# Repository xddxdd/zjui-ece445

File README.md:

Air Quality Sensing Network
===========================

Cloud Server Installation
-------------------------

1. I do not recommend using a cloud server located in mainland China, since then you need to register with the government (备案) to host a website.
   - You may choose servers located in Hong Kong, for example.
2. Install InfluxDB
   - [https://docs.influxdata.com/influxdb/v1.8/introduction/install/](https://docs.influxdata.com/influxdb/v1.8/introduction/install/)
3. Create a database named `air_quality`.
4. Create 3 users:
   - [https://docs.influxdata.com/influxdb/v1.8/administration/authentication_and_authorization/](https://docs.influxdata.com/influxdb/v1.8/administration/authentication_and_authorization/)
   - The first is administrator for InfluxDB server.
   - The second is for sensors to upload data.
     - Username: `***REMOVED***`
     - Password: `***REMOVED***`
   - The third is for website system to read data.
     - Username: `***REMOVED***`
     - Password: `***REMOVED***`
5. Make sure you can access InfluxDB via `[Server IP]:8086`.

STM32 Installation
------------------

1. Modify `stm32/Src/run.h`:
   - Change `HTTP_INFLUXDB_IP` etc to point to your cloud server
   - If you changed username or password for the upload user, also update them here
   - Change `ZJUWLAN_USERNAME` and `ZJUWLAN_PASSWORD` to your own, for auto login to ZJU Wi-Fi
2. Run `make` in `stm32` directory.
   - I'm assuming you use Mac or Linux. I never tried to compile the project on Windows.
   - You need to download GNU Arm Embedded Toolchain.
3. Put the jumper on the top of STM32 (closer to the 4 unsoldered holes) to right, to enter download mode
4. Connect a serial to USB converter:
   - PA9 (GPS module's TX) - Converter's RX
   - PA10 (GPS module's RX) - Converter's TX
   - Ground pin (choose any one) - Converter's GND
5. Run following command to flash program to STM32:
   - `stm32flash /dev/ttyUSB0 -w build/stm32.bin -v -g 0x0`
   - Now the program should start running
6. If you want to put STM32 to field-test, put the jumper on the top of STM32 to left, to enter normal working mode
   - Now STM32 will start running the flashed program once power is on
7. You can use STM32CubeMX to open the `stm32/stm32.ioc` project to change pin definition, regenerate library code, etc.

Web Server Installation
-----------------------

1. Install nginx and PHP on the cloud server:
   - [https://www.digitalocean.com/community/tutorials/how-to-install-linux-nginx-mysql-php-lemp-stack-ubuntu-18-04](https://www.digitalocean.com/community/tutorials/how-to-install-linux-nginx-mysql-php-lemp-stack-ubuntu-18-04)
   - Point website root folder to `webpage` folder.
2. Install Python 3 on the server, and libraries that are needed:
   - `apt install python3 python3-pip python3-numpy python3-matplotlib `
   - `pip3 install influxdb windrose`
3. Enter `python` directory, run `python3 run.py` to refresh website.
   - Remember to update InfluxDB address/user/password in `fetch.py`.
   - Use tools such as Cron or Systemd to run it periodically.
4. Run `python3 weatherlink.py` to crawl wind direction & speed from weather station and upload to InfluxDB.
   - Also remember to update InfluxDB address/user/password in `weatherlink.py`.
   - Use tools such as Supervisord or Systemd to run it continuously.

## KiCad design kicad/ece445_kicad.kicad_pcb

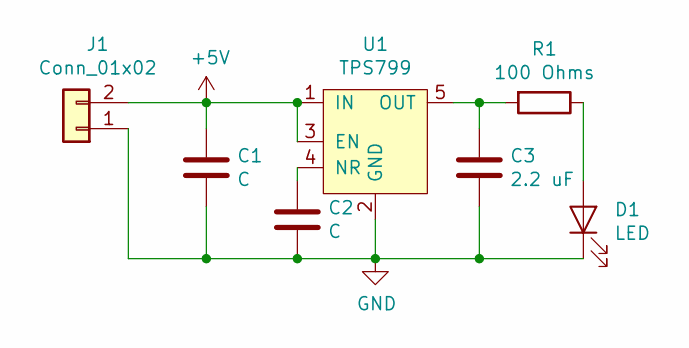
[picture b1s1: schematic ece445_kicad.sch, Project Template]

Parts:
C1, C2: C; CP_Radial_D5.0mm_P2.50mm
C3: 2.2 uF; CP_Radial_D5.0mm_P2.50mm
D1: LED; LED_Rectangular_W5.0mm_H2.0mm
J1: Conn_01x02; PinHeader_1x02_P2.54mm_Vertical
R1: 100 Ohms; R_Axial_DIN0204_L3.6mm_D1.6mm_P5.08mm_Horizontal
U1: TPS799

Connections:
+5V: C1.1, J1.2, U1.1 (IN), U1.3 (EN)
GND: C1.2, C2.2, C3.2, D1.1 (K), J1.1, U1.2 (GND)
unnamed: C2.1, U1.4 (NR)
unnamed: C3.1, R1.2, U1.5 (OUT)
unnamed: D1.2 (A), R1.1

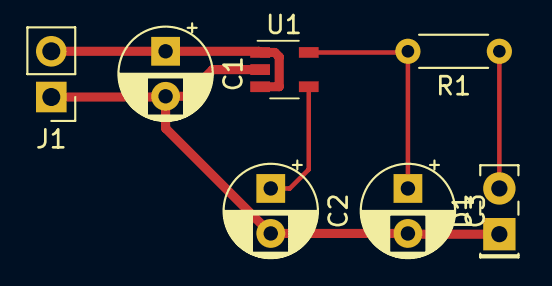
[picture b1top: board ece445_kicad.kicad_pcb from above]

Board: 2 copper layers, 7 parts (0 on the bottom side), 5 nets.

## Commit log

2020-03-21 PCB assignment
2020-03-31 stm32: blinker working
2020-03-31 stm32: i2c work in progress
2020-03-31 stm32: bme680 almost working
2020-03-31 stm32: bme680 fully working
2020-03-31 stm32: remove build files from repo
2020-03-31 stm32: general coding style fixes
2020-03-31 stm32: code simplification
2020-03-31 stm32: adc works
2020-04-14 Add value conversion
2020-04-17 stm32: pms5003 working
2020-04-17 stm32: general cleanup
2020-04-17 stm32: stop mode and rtc wakeup
2020-04-21 stm32: update mics6814 formula
2020-04-21 stm32: add IAQ calculation
2020-04-21 stm32: use BSEC for BME680 (still dont work)
2020-04-21 stm32: bme680 bsec work, switch to printf
2020-04-21 stm32: code cleanup
2020-04-24 stm32: send results over TCP
2020-04-25 stm32: reduce code size
2020-04-25 stm32: further shrink binary size
2020-04-25 stm32: fix mics6814 formula
2020-04-25 stm32: upload to influxdb, pseudo rng for session id
2020-04-26 stm32: try to fix mics6814 (but failed)
2020-04-26 stm32: esp8266 powersave optimization
2020-05-01 stm32: add experimental gps
2020-05-01 stm32: shrink code size in progress
2020-05-01 stm32: use LL driver for RCC to shrink binary size
2020-05-01 stm32: blink when waiting for gps
2020-05-01 stm32: add gps debugging
2020-05-01 stm32: remove unneeded library files
2020-05-01 stm32: update project
2020-05-02 stm32: confirm gps works
2020-05-05 datasheets: add
2020-05-05 stm32: add pin definition (unused for now)
2020-05-06 stm32: adopt for ZJUWLAN network
2020-05-14 map algorithm added
2020-05-14 stm32: add mosfet control & vbat measurement & conversion
2020-05-22 stm32: multiple changes
2020-05-22 webpage: initial commit
2020-05-22 stm32: influxdb bugfix
2020-05-22 stm32: gps reporting bugfix
2020-05-23 stm32: trigger battery module periodically, further reduce frequency
2020-05-23 python: add script to fetch data from influxdb
2020-05-23 map.py Load file function added
2020-05-23 webpage: add forecast select bar & data download
2020-05-23 python: add script to download wind direction
2020-05-23 python: upload weatherlink data to influxdb
2020-05-24 webpage: use local scripts
2020-05-25 windrose map added
2020-05-25 exit safely
2020-05-25 webpage & stm32: update
2020-05-25 webpage: realtime display and fixes
2020-05-26 webpage & python: show data points & fix map
2020-05-26 webpage & python: windrose & style change
2020-05-26 webpage & python: color bar
2020-05-26 webpage: minor style update
2020-05-26 add battery plot script
2020-05-26 webpage: minor style change
2020-05-27 webpage: fix display on chrome
2020-06-01 general: cleanup before handover project
